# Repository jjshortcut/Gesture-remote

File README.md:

# Gesture-remote
Gesture remote 433MZ with APDS-9960
The gestures are used to control a klikaan-klikuit (socket with remote) set

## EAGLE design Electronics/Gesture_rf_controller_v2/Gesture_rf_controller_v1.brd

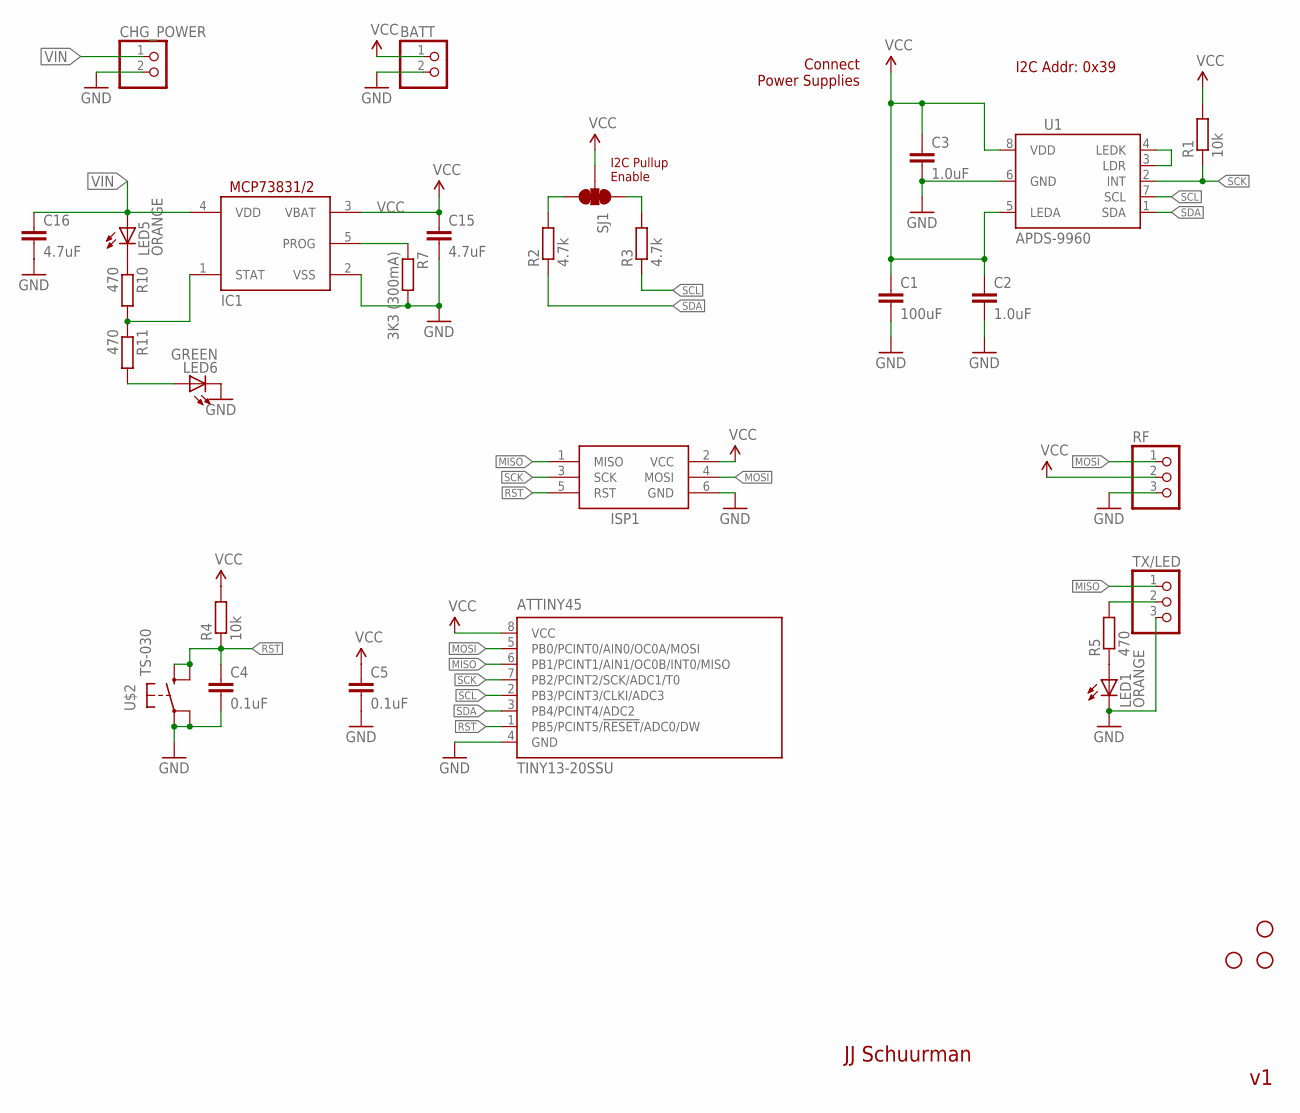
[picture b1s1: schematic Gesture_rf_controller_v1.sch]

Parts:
ATTINY45: TINY13-20SSU; 8S1
BATT: PINHD-1X2; 1X02
C1: 100uF; C0805
C2, C3: 1.0uF; C0805
C4: 0.1uF; C1206
C5: 0.1uF; C0805
C15, C16: 4.7uF; C0805K
CHG_POWER: PINHD-1X2; 1X02
IC1: MCP73831/OT; SOT23-5L
ISP1: AVRISP-6; AVRISP
LED1: ORANGE; CHIP-LED0805
LED5: ORANGE; CHIPLED_0805
LED6: GREEN; CHIPLED_0805
R1: 10k; R0805
R2, R3: 4.7k; R1206
R4: 10k; M0805
R5: 470; R0805
R7: 3K3 (300mA); M1206
R10, R11: 470; M0805
RF: PINHD-1X3; 1X03
SJ1: SOLDERJUMPER_2WAYPASTE1&2&3; SJ_3_PASTE1&2&3
STANDOFF1, STANDOFF2, STANDOFF4: STAND-OFF
TX/LED: PINHD-1X3; 1X03
U1: APDS-9960
U$2: TS-030

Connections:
GND: ATTINY45.4 (GND), BATT.2, C1.2, C2.2, C3.2, C4.2, C5.2, C15.2, C16.2, CHG_POWER.2, IC1.2 (VSS), ISP1.6 (GND), LED1.C, LED6.C, R7.2, RF.3, TX/LED.3, U1.6 (GND), U$2.P$2 (1), U$2.P$3 (2)
MISO: ATTINY45.6 (PB1/PCINT1/AIN1/OC0B/INT0/MISO), ISP1.1 (MISO), TX/LED.1
MOSI: ATTINY45.5 (PB0/PCINT0/AIN0/OC0A/MOSI), ISP1.4 (MOSI), RF.1
unnamed: R2.2, SJ1.3
unnamed: R3.2, SJ1.1
unnamed: LED1.A, R5.1
unnamed: U1.3 (LDR), U1.4 (LEDK)
unnamed: IC1.5 (PROG), R7.1
unnamed: LED5.C, R10.1
unnamed: IC1.1 (STAT), R10.2, R11.1
unnamed: LED6.A, R11.2
RST: ATTINY45.1 (PB5/PCINT5/!RESET!/ADC0/DW), C4.1, ISP1.5 (RST), R4.1, U$2.P$1 (3), U$2.P$4 (4)
SCK: ATTINY45.7 (PB2/PCINT2/SCK/ADC1/T0), ISP1.3 (SCK), R1.1, U1.2 (INT)
SCL: ATTINY45.2 (PB3/PCINT3/CLKI/ADC3), R3.1, U1.7 (SCL)
SDA: ATTINY45.3 (PB4/PCINT4/ADC2), R2.1, U1.1 (SDA)
TX/LED: R5.2, TX/LED.2
VCC: ATTINY45.8 (VCC), BATT.1, C1.1, C2.1, C3.1, C5.1, C15.1, IC1.3 (VBAT), ISP1.2 (VCC), R1.2, R4.2, RF.2, SJ1.2, U1.5 (LEDA), U1.8 (VDD)
VIN: C16.1, CHG_POWER.1, IC1.4 (VDD), LED5.A

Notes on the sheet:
JJ Schuurman
I2C Addr: 0x39
I2C Pullup Enable
Connect Power Supplies

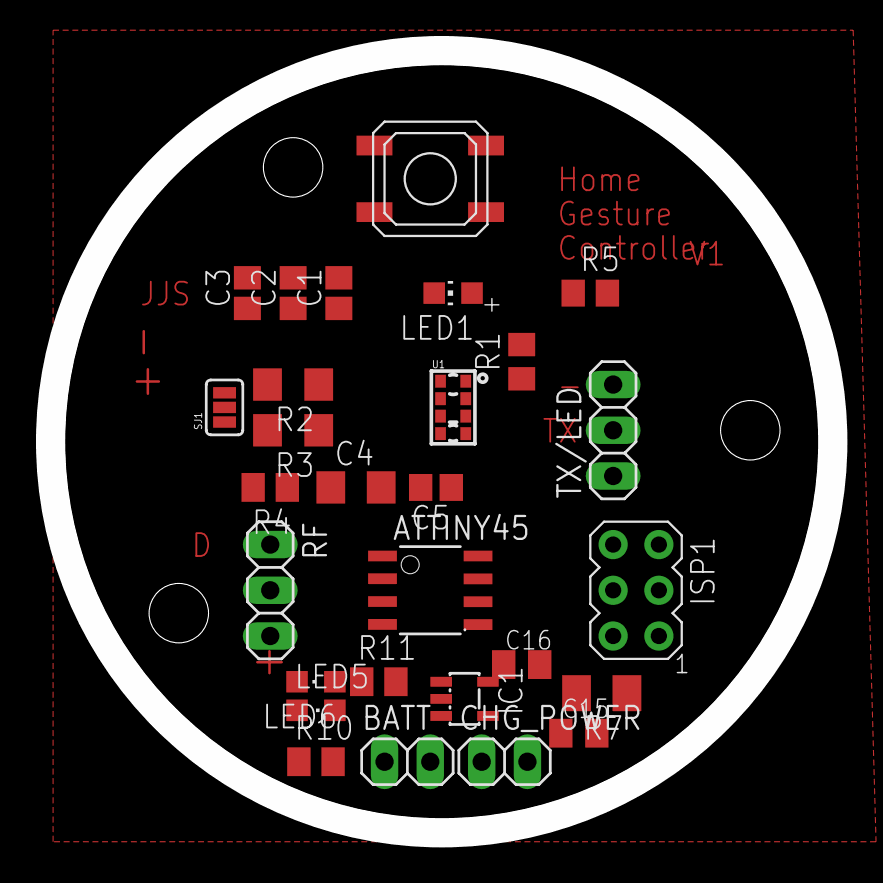
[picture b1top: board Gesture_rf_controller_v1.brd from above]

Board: 2 copper layers, 43.5 x 43.5 mm, 31 parts (0 on the bottom side), 18 nets.

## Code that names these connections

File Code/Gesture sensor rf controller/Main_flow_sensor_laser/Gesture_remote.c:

/*
 * Main_flow_sensor_laser.c
 *
 * Created: 5/20/2014 9:16:13 PM
 *  Author: Jan-Jaap
 *
 *	@4.8MHZ/8 - 600Khz (now @ 1Mhz with attiny85)
 *  Brownout @4.3v
 *	Pinout:
 *	PB0 = RF433 MHz sender
 *	PB1 = TX debug 9600 8N1, LED
 *	PB2 = INT0, for gesture chip ADPS-9960
 *	PB3 = SCL I2C ADPS-9960
 *	PB4 = SDA I2C ADPS-9960
 *	PB5 = Reset
 *
 */ 

#include <stdlib.h> 
#include <avr/io.h>
#include <avr/interrupt.h>
#include <util/delay.h>
#include <avr/sleep.h>

#include <avr/pgmspace.h>
#include "dbg_putchar.h"
#include "Klikaan_klikuit.h"
#include "APDS9960.h"

#define APDS9960_INT	PB2 // Needs to be an interrupt pin

#define FLOW_THRESHOLD 4	// Threshold of output vs. flow
#define EXT_AS_LED_SWITCH 1

#define BLINK_DELAY_MS 250
#define LONG_DELAY 500
#define SHORT_DELAY 150
#define DEBUG_MSG 1

/* Pinouts */
/* PB1 = serial debug TX defined in dbg_putchar.c */

// Use jumper to enable led (no TX then)
#define LED_PIN PB1
#define LED_ON	(PORTB |= (1 << LED_PIN))		// LED on
#define LED_OFF	(PORTB &= ~(1 << LED_PIN))		// LED off
#define LED_TOGGLE (PORTB ^= (1 << LED_PIN))		// LED toggle

// Prototypes
void init_IO(void);
void init_interrupt(void);
void send_start_settings(void);
void uart_puts(const char *s);				// Print strings from RAM 
void uart_puts_p(const char *progmem_s);	// Print strings from PROGMEM (FLASH)
void blink(uint8_t nr_of_blinks, uint16_t delay_ms);
void LED_alarm(void);
void my_delay_ms(uint8_t n);
void handleGesture(void); 
void disable_gesture_int(uint8_t interrupt);
void klikaan_klikuit_off(void);
void do_sleep(void);

volatile uint8_t int_flag = 0;
uint8_t a_flag = 0, b_flag = 0, c_flag = 0, d_flag = 0, e_flag = 0;

ISR (INT0_vect)
{
	// Do something?
	int_flag = 1;
	//uart_puts("int!\n");
	//LED_TOGGLE;
}

int main(void)
{
	//unsigned char i2cdata[8];
	init_IO();
	#if(DEBUG_MSG)
	{
		dbg_tx_init();
	}
	#else
	{
		blink(4, SHORT_DELAY);
	}
	#endif
	
	init_klikaan_klikuit();
	klikaan_klikuit_off();	// all klikaan off
	
	#if DEBUG_MSG
	send_start_settings();
	#endif
	init_interrupt();// first enable interrupt RUN FIRST??
	
	if (init_apds()) 
	{
		#if DEBUG_MSG
		uart_puts_p(PSTR("APDS-9960 init complete!\n"));
		#endif
	} 
	else 
	{
		#if DEBUG_MSG
		uart_puts_p(PSTR("APDS-9960 init failed!\n"));
		#endif
	}
	
	if (enableGestureSensor(1))
	{
		#if DEBUG_MSG
		uart_puts_p(PSTR("Gesture sensor now running!\n"));
		#endif
	}
	else
	{
		#if DEBUG_MSG
		uart_puts_p(PSTR("Something went wrong during gesture sensor init!"));
		#endif
	}

	while(1) 
	{
		if (int_flag)
		{
			disable_gesture_int(true);	// disable
			uart_puts_p(PSTR("Int trig!\n"));
			handleGesture();
			int_flag = 0;
			disable_gesture_int(false);	// enable
		}
		//uart_puts("go to sleep\n");
		//do_sleep();	// sleep until int0 trigger
		
		//send_klikaan_klikuit(c_off_1);
	}	
}

void init_IO(void)
{
	DDRB |= (1<<LED_PIN);					// Output pin for LED
}

void init_interrupt(void)	// int of apds9960
{
	GIMSK |= (1<<INT0);		// Enable INT0
	MCUCR |= (1<<ISC01);	// INT0 on Falling edge
	//MCUCR |= (1<<ISC01);	// Any change
	sei();					// Enable global interrupts
}	

void klikaan_klikuit_off(void)
{
	a_flag=0;
	b_flag=0;
	c_flag=0;
	d_flag=0;
	e_flag=0;
	send_klikaan_klikuit(a_off_1);
	send_klikaan_klikuit(b_off_1);
	send_klikaan_klikuit(c_off_1);
	send_klikaan_klikuit(d_off_1);
	send_klikaan_klikuit(e_off_1);
}

void disable_gesture_int(uint8_t interrupt)
{
	if (!interrupt)	// enable
	{
		GIMSK |= (1<<INT0);		// Enable INT0	
	}
	else  // Disable
	{
		GIMSK &= ~(1<<INT0);		// Disable INT0
	}
}

void send_start_settings(void)
{
	uart_puts_p(PSTR("Gesture recognition APDS-9960 chip test v1.0\n"));
}

void my_delay_ms(uint8_t n) 
{
	while(n--) {
		_delay_us(1);
	}
}

void blink(uint8_t nr_of_blinks, uint16_t delay_ms)
{
	uint16_t delay_time_ms = BLINK_DELAY_MS;
	if ((delay_ms > 0) && (delay_ms <= 5000))	// delay should not be more than 5 sec..
	{
		delay_time_ms = delay_ms;
		if (nr_of_blinks<2)	// if 1 blink
		{
			LED_ON;
			for (int16_t i=0;i<(delay_time_ms);i++)
			{
				_delay_ms(1);
			}
			LED_OFF;
		}
		else
		{
			for (int i=0;i<nr_of_blinks;i++)
			{
				LED_ON;
				for (int16_t i=0;i<(delay_time_ms/2);i++)
				{
					_delay_ms(1);
				}
				//_delay_ms(delay_time_ms);
				LED_OFF;
				for (int16_t i=0;i<(delay_time_ms/2);i++)
				{
					_delay_ms(1);
				}
				//_delay_ms(delay_time_ms);
			}
		}
	}
}

void handleGesture(void) 
{
	if ( isGestureAvailable() ) 
	{
		switch ( readGesture() ) 
		{
			case DIR_UP:
				#if DEBUG_MSG
				uart_puts("UP:");
				#endif
				if (a_flag) {
					//send_klikaan_klikuit(a_off_1);
					#if DEBUG_MSG
					uart_puts("A OFF\n");
					#else
					blink(1, SHORT_DELAY);
					#endif
					a_flag=0;
				}
				else {
					//send_klikaan_klikuit(a_on_1);
					#if DEBUG_MSG
					uart_puts("A ON\n");
					#else
					blink(1, SHORT_DELAY);
					#endif
					a_flag=1;
				}
			break;
			case DIR_DOWN:
				#if DEBUG_MSG
				uart_puts("DOWN:");
				#endif
				if (c_flag) {
					//send_klikaan_klikuit(c_off_1);
					#if DEBUG_MSG
					uart_puts("C OFF\n");
					#else
					blink(3, SHORT_DELAY);
					#endif
					c_flag=0;
				}
				else {
					//send_klikaan_klikuit(c_on_1);
					#if DEBUG_MSG
					uart_puts("C ON\n");
					#else
					blink(3, SHORT_DELAY);
					#endif
					c_flag=1;
				}
			break;
			case DIR_LEFT:
				#if DEBUG_MSG
				uart_puts("LEFT: ");
				#endif
				if (d_flag) {
					//send_klikaan_klikuit(d_off_1);
					#if DEBUG_MSG
					uart_puts("D OFF\n");
					#else
					blink(4, SHORT_DELAY);
					#endif
					d_flag=0;
				}
				else {
					//send_klikaan_klikuit(d_on_1);
					#if DEBUG_MSG
					uart_puts("D ON\n");
					#else
					blink(4, SHORT_DELAY);
					#endif
					d_flag=1;
				}
			break;
			case DIR_RIGHT:
				#if DEBUG_MSG
				uart_puts("RIGHT:");
				#endif
				if (b_flag) {
					//send_klikaan_klikuit(b_off_1);
					#if DEBUG_MSG
					uart_puts("B OFF\n");
					#else
					blink(3, SHORT_DELAY);
					#endif
					b_flag=0;
				}
				else {
					//send_klikaan_klikuit(b_on_1);
					#if DEBUG_MSG
					uart_puts("B ON\n");
					#else
					blink(3, SHORT_DELAY);
					#endif
					b_flag=1;
				}
			break;
			case DIR_NEAR:
				#if DEBUG_MSG
				uart_puts("NEAR:");
				#endif
			break;
			case DIR_FAR:
				#if DEBUG_MSG
				uart_puts("FAR:");
				#endif
				//klikaan_klikuit_off();
				#if DEBUG_MSG
				uart_puts("ALL OFF\n");
				#else
				blink(5 ,SHORT_DELAY);
				#endif
			break;
			case ERROR:
				#if DEBUG_MSG
				uart_puts("ERROR!\n");
				#else
				blink(1, LONG_DELAY);
				#endif
			break;
			default:
				#if DEBUG_MSG
				uart_puts("NONE\n");
				#else
				blink(1, LONG_DELAY);
				#endif
		}
	}
}

void do_sleep()
{
	ADCSRA	&= ~(1 << ADEN);					// Disable ADC, save power
	ACSR |= _BV(ACD);							//disable the analog comparator
	//PRR |= (1 << PRTIM1) | (1 << PRTIM0) | (1 << PRUSI) | (1 << PRADC); // Power down all peripherals ALSO TIMERS!
	set_sleep_mode(SLEEP_MODE_PWR_DOWN);		// MCU into power-down mode
	sleep_enable();								// Set sleep enable (SE) bit
	//GIMSK |= (1<<INT0);							// enable INT0
	init_interrupt();
	//sleep_bod_disable();						// Put the device to sleep
	//sei();
	sleep_cpu();			// Put the device to sleep
	cli();
	uart_puts("wakeup!\n");
	sleep_disable();		// Upon waking up, sketch continues from this point
	sei();					// Keep int0 enabled!
	init_klikaan_klikuit();
}

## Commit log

2017-05-23 Inital commit of gesture remote

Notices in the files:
parts and their libraries:
SparkFun-Aesthetics: Licensing: Creative Commons ShareAlike 4.0 International - https://creativecommons.org/licenses/by-sa/4.0
